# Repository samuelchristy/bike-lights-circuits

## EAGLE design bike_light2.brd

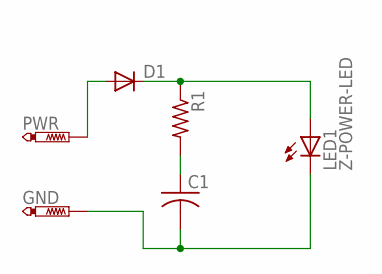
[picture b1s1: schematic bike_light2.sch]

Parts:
C1: SUPERCAP5.5_1FDGH; CAP_1UF_DGH
D1: DIODE-DO-214AC; DO-214AC
GND: PTR1PAD1-13Y; P1-13Y
LED1: Z-POWER-LED; Z-POWER-LED-PCB-TYPE
PWR: PTR1PAD1-13Y; P1-13Y
R1: R-US_M1206; M1206

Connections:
GND: C1.P$2 (2), GND.TP, LED1.C
unnamed: D1.C, LED1.A, R1.1
unnamed: D1.A, PWR.TP
unnamed: C1.P$1 (1), R1.2

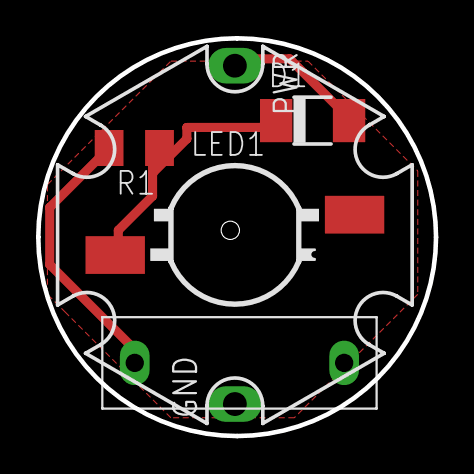
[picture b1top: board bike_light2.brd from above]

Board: 2 copper layers, 22.1 x 22.1 mm, 6 parts (0 on the bottom side), 4 nets.

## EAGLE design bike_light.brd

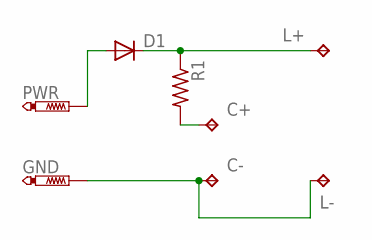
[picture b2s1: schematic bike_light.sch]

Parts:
C+: TPTP20SQ; TP20SQ
C-: TPTP20SQ; TP20SQ
D1: DIODE-DO-214AC; DO-214AC
GND: PTR1PAD1-13Y; P1-13Y
L+: TPTP20SQ; TP20SQ
L-: TPTP20SQ; TP20SQ
PWR: PTR1PAD1-13Y; P1-13Y
R1: R-US_M1206; M1206

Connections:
unnamed: D1.C, L+.TP, R1.1
unnamed: C+.TP, R1.2
unnamed: C-.TP, GND.TP, L-.TP
unnamed: D1.A, PWR.TP

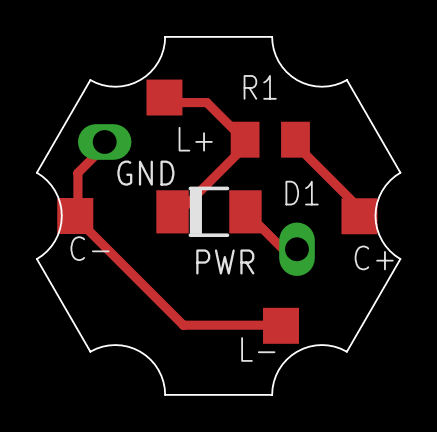
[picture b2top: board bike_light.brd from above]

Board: 2 copper layers, 20.2 x 19.9 mm, 8 parts (0 on the bottom side), 4 nets.

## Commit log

2019-03-06 Updated lights
2019-03-14 Latest light after the first build.
